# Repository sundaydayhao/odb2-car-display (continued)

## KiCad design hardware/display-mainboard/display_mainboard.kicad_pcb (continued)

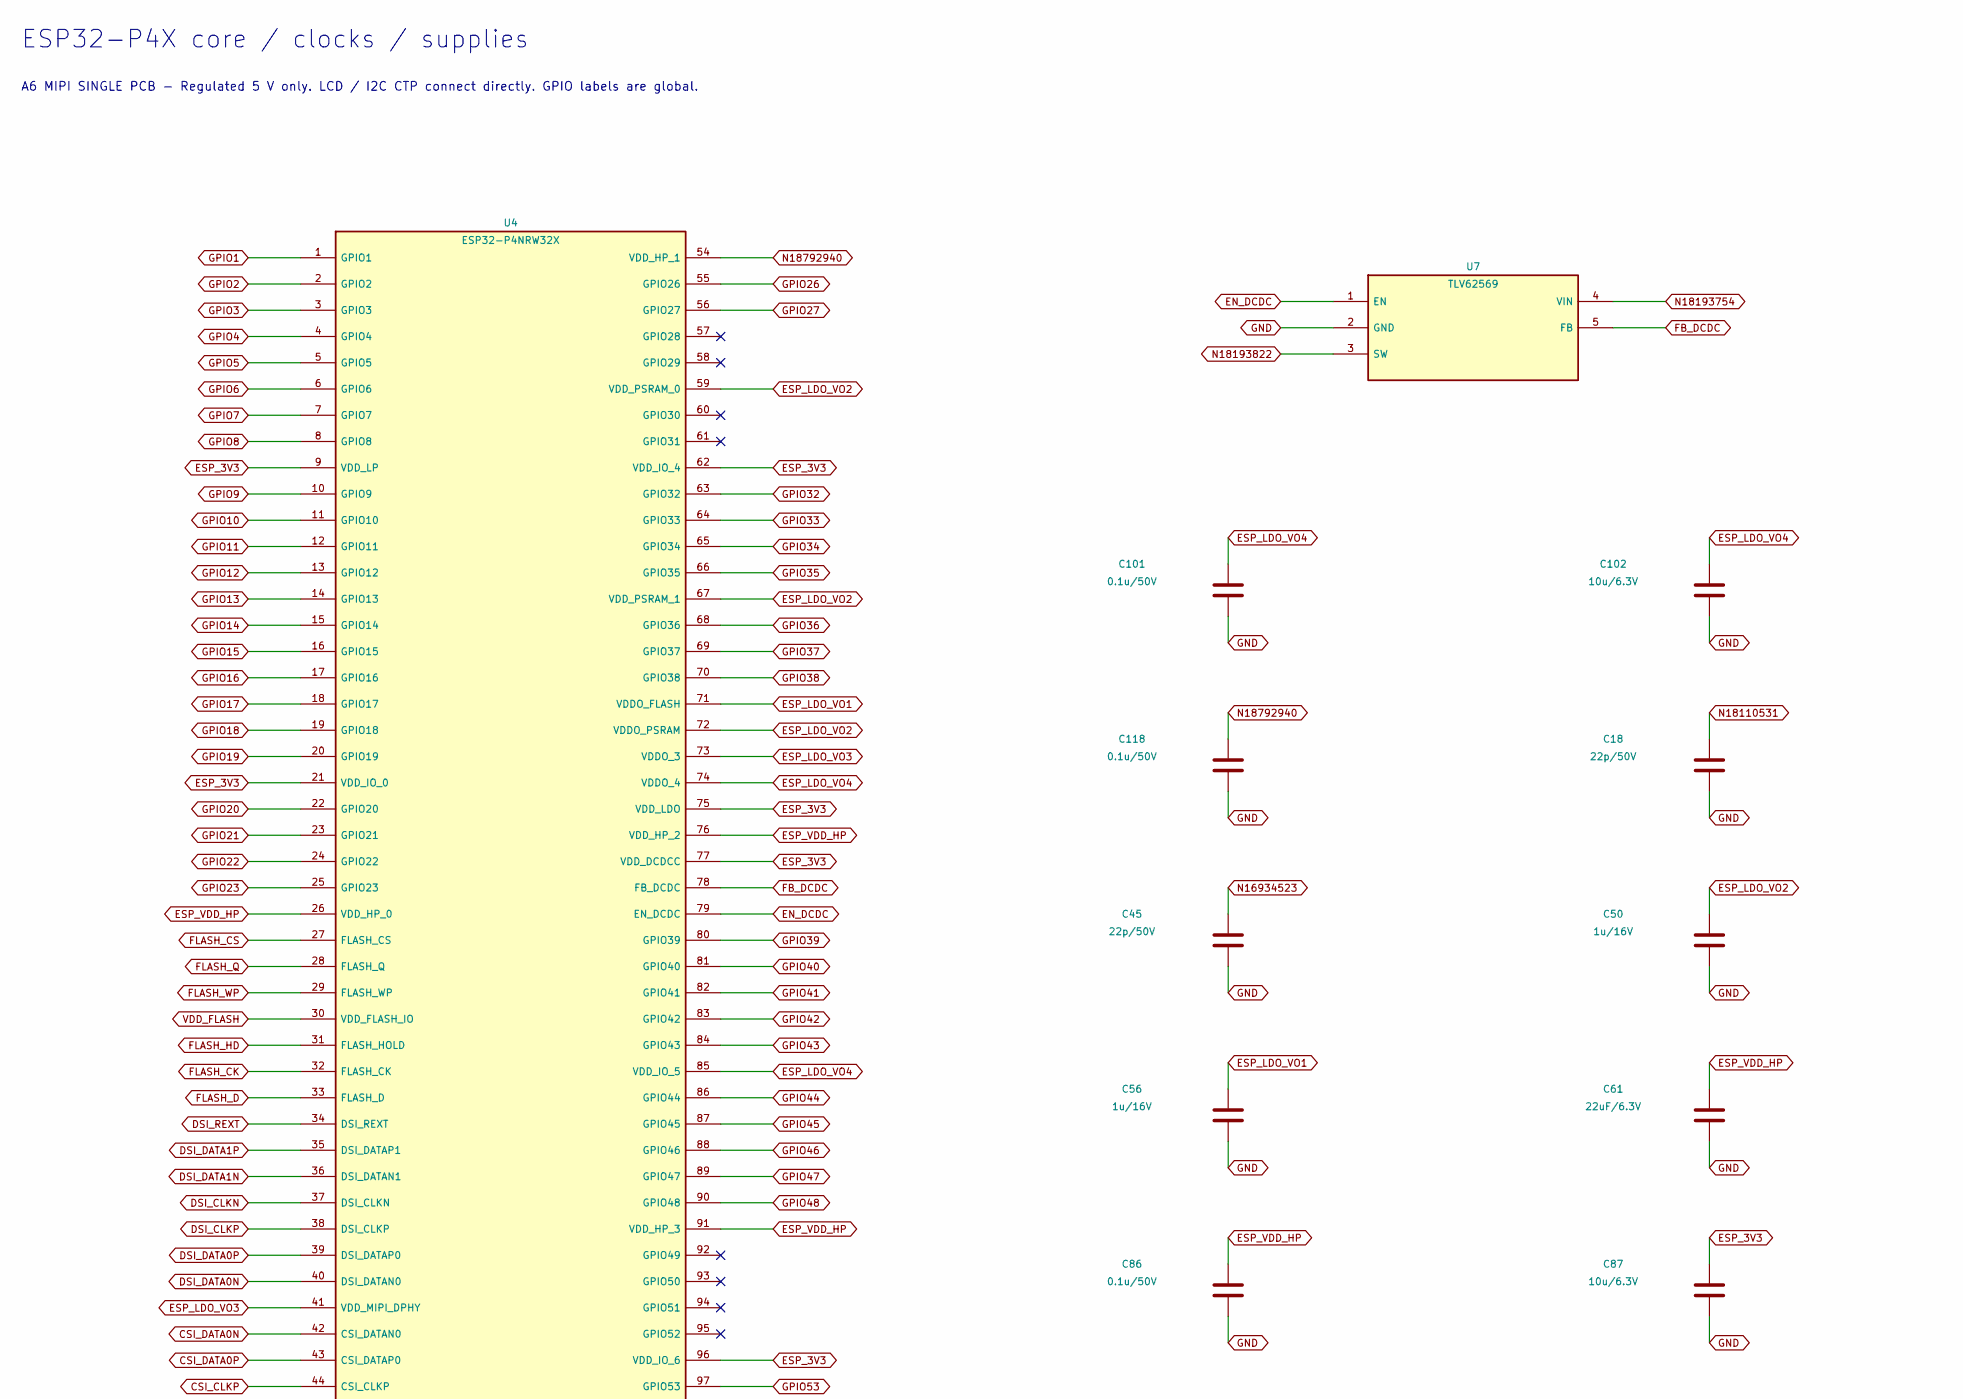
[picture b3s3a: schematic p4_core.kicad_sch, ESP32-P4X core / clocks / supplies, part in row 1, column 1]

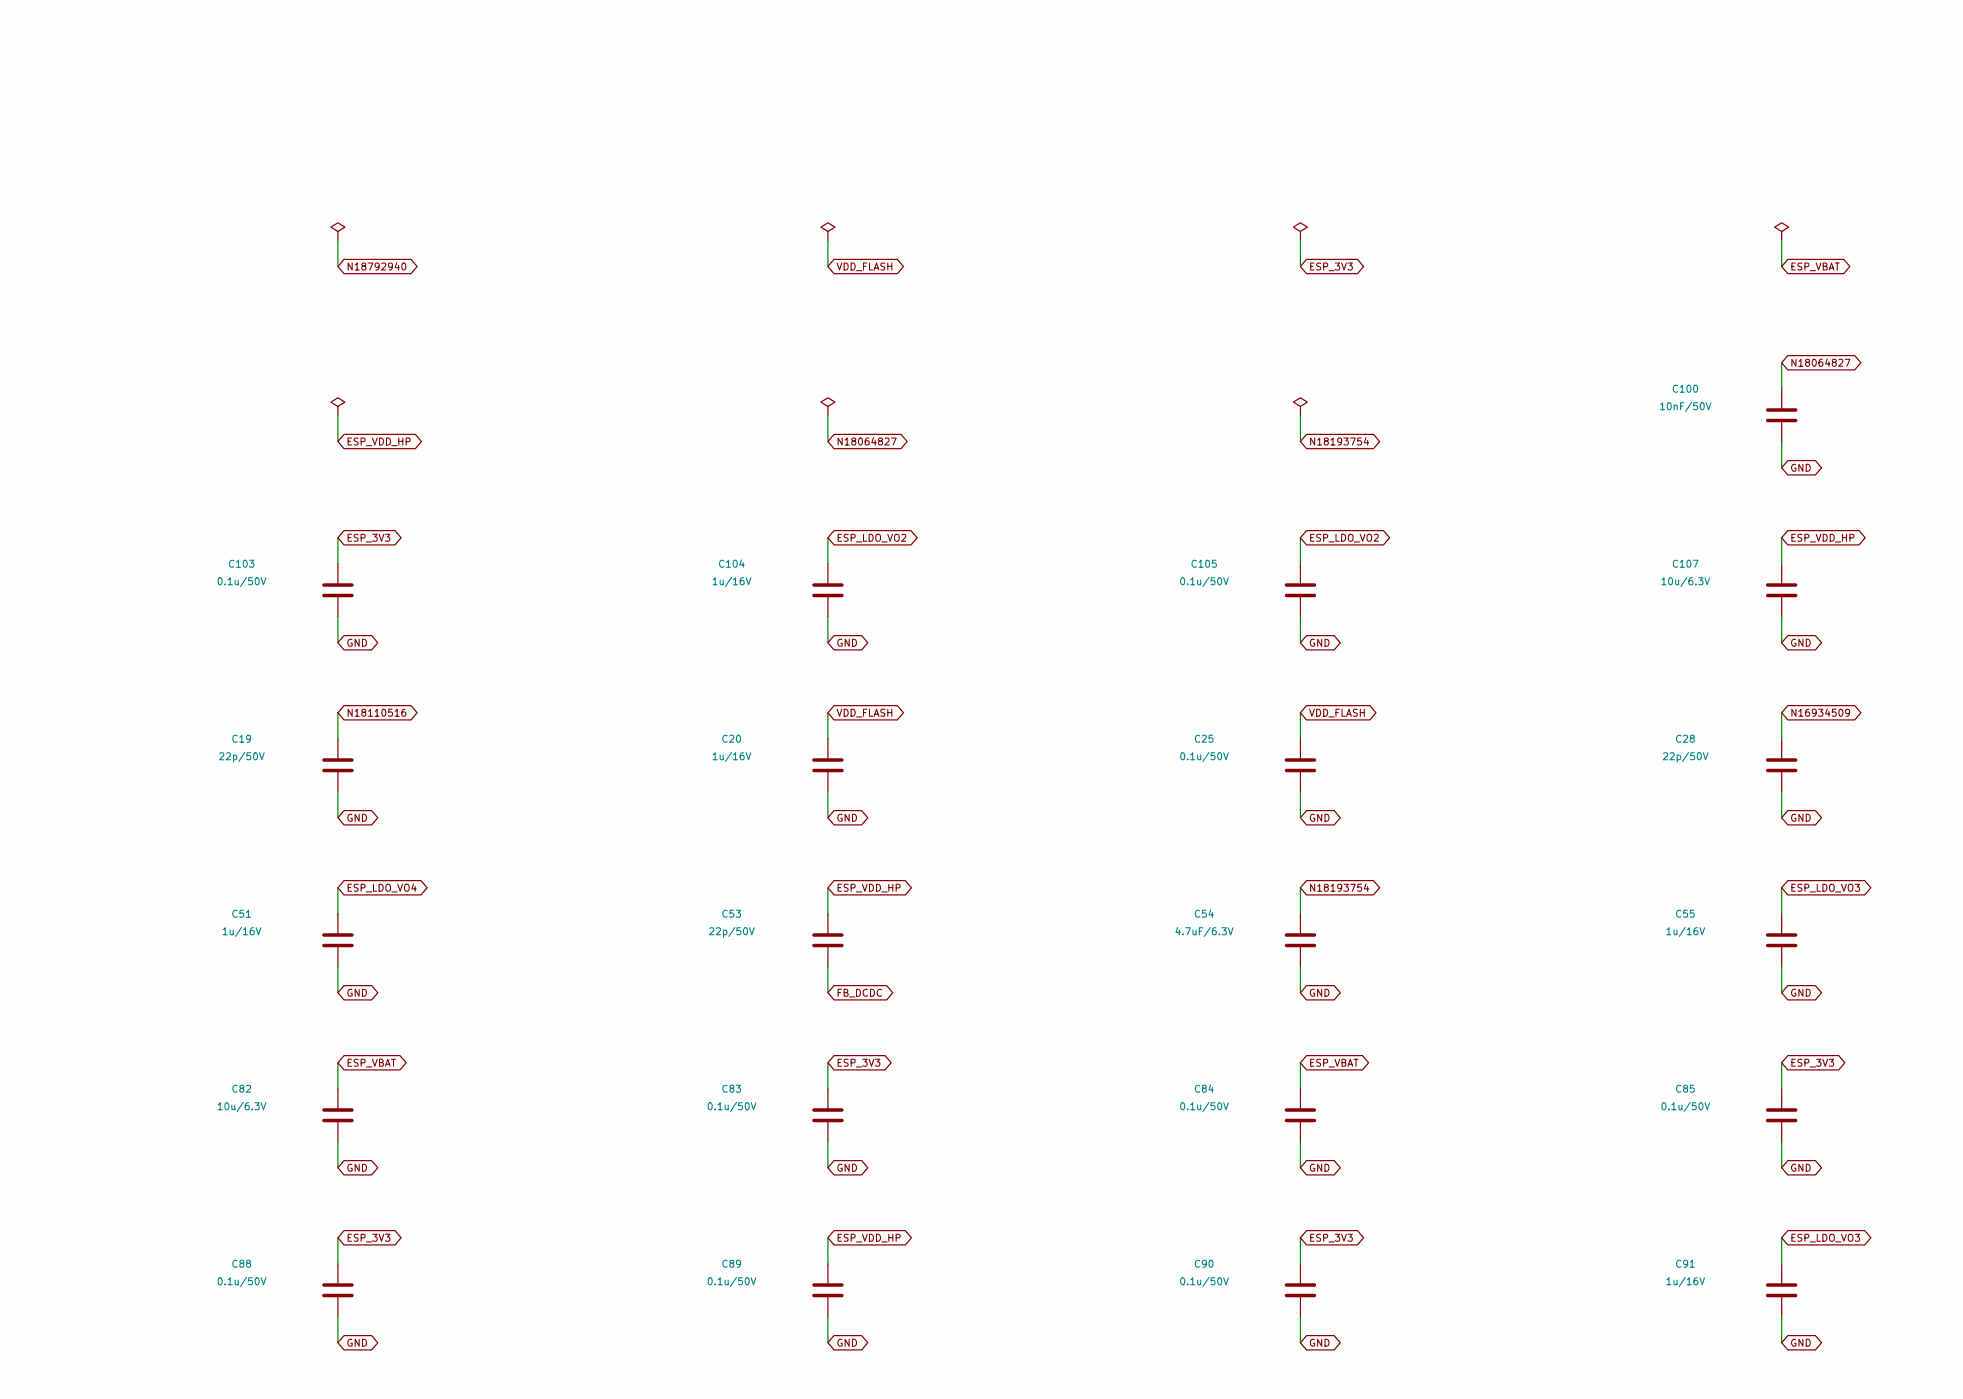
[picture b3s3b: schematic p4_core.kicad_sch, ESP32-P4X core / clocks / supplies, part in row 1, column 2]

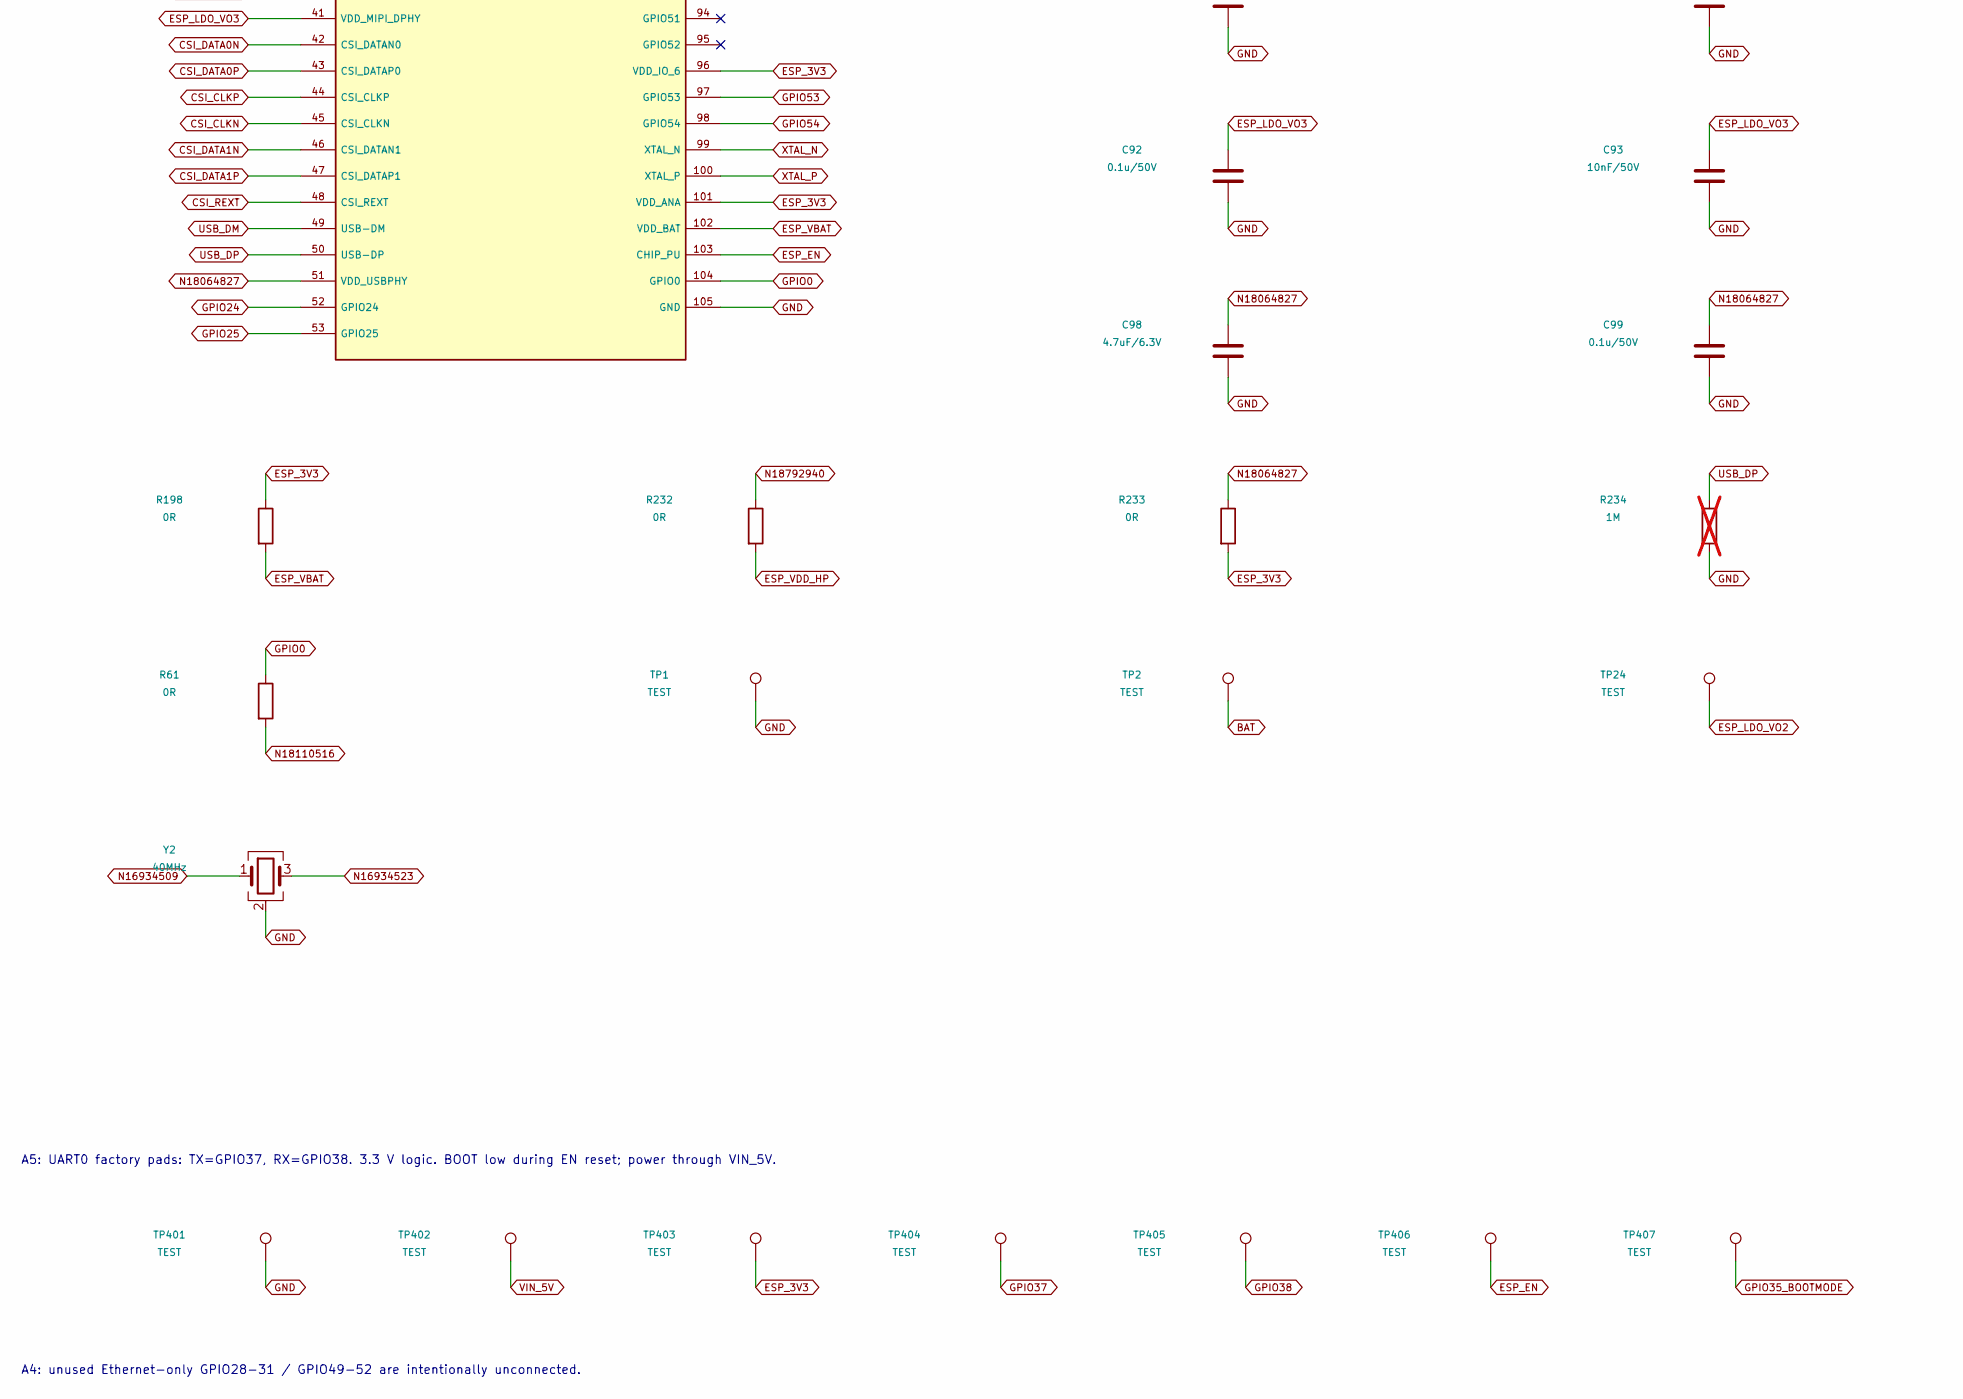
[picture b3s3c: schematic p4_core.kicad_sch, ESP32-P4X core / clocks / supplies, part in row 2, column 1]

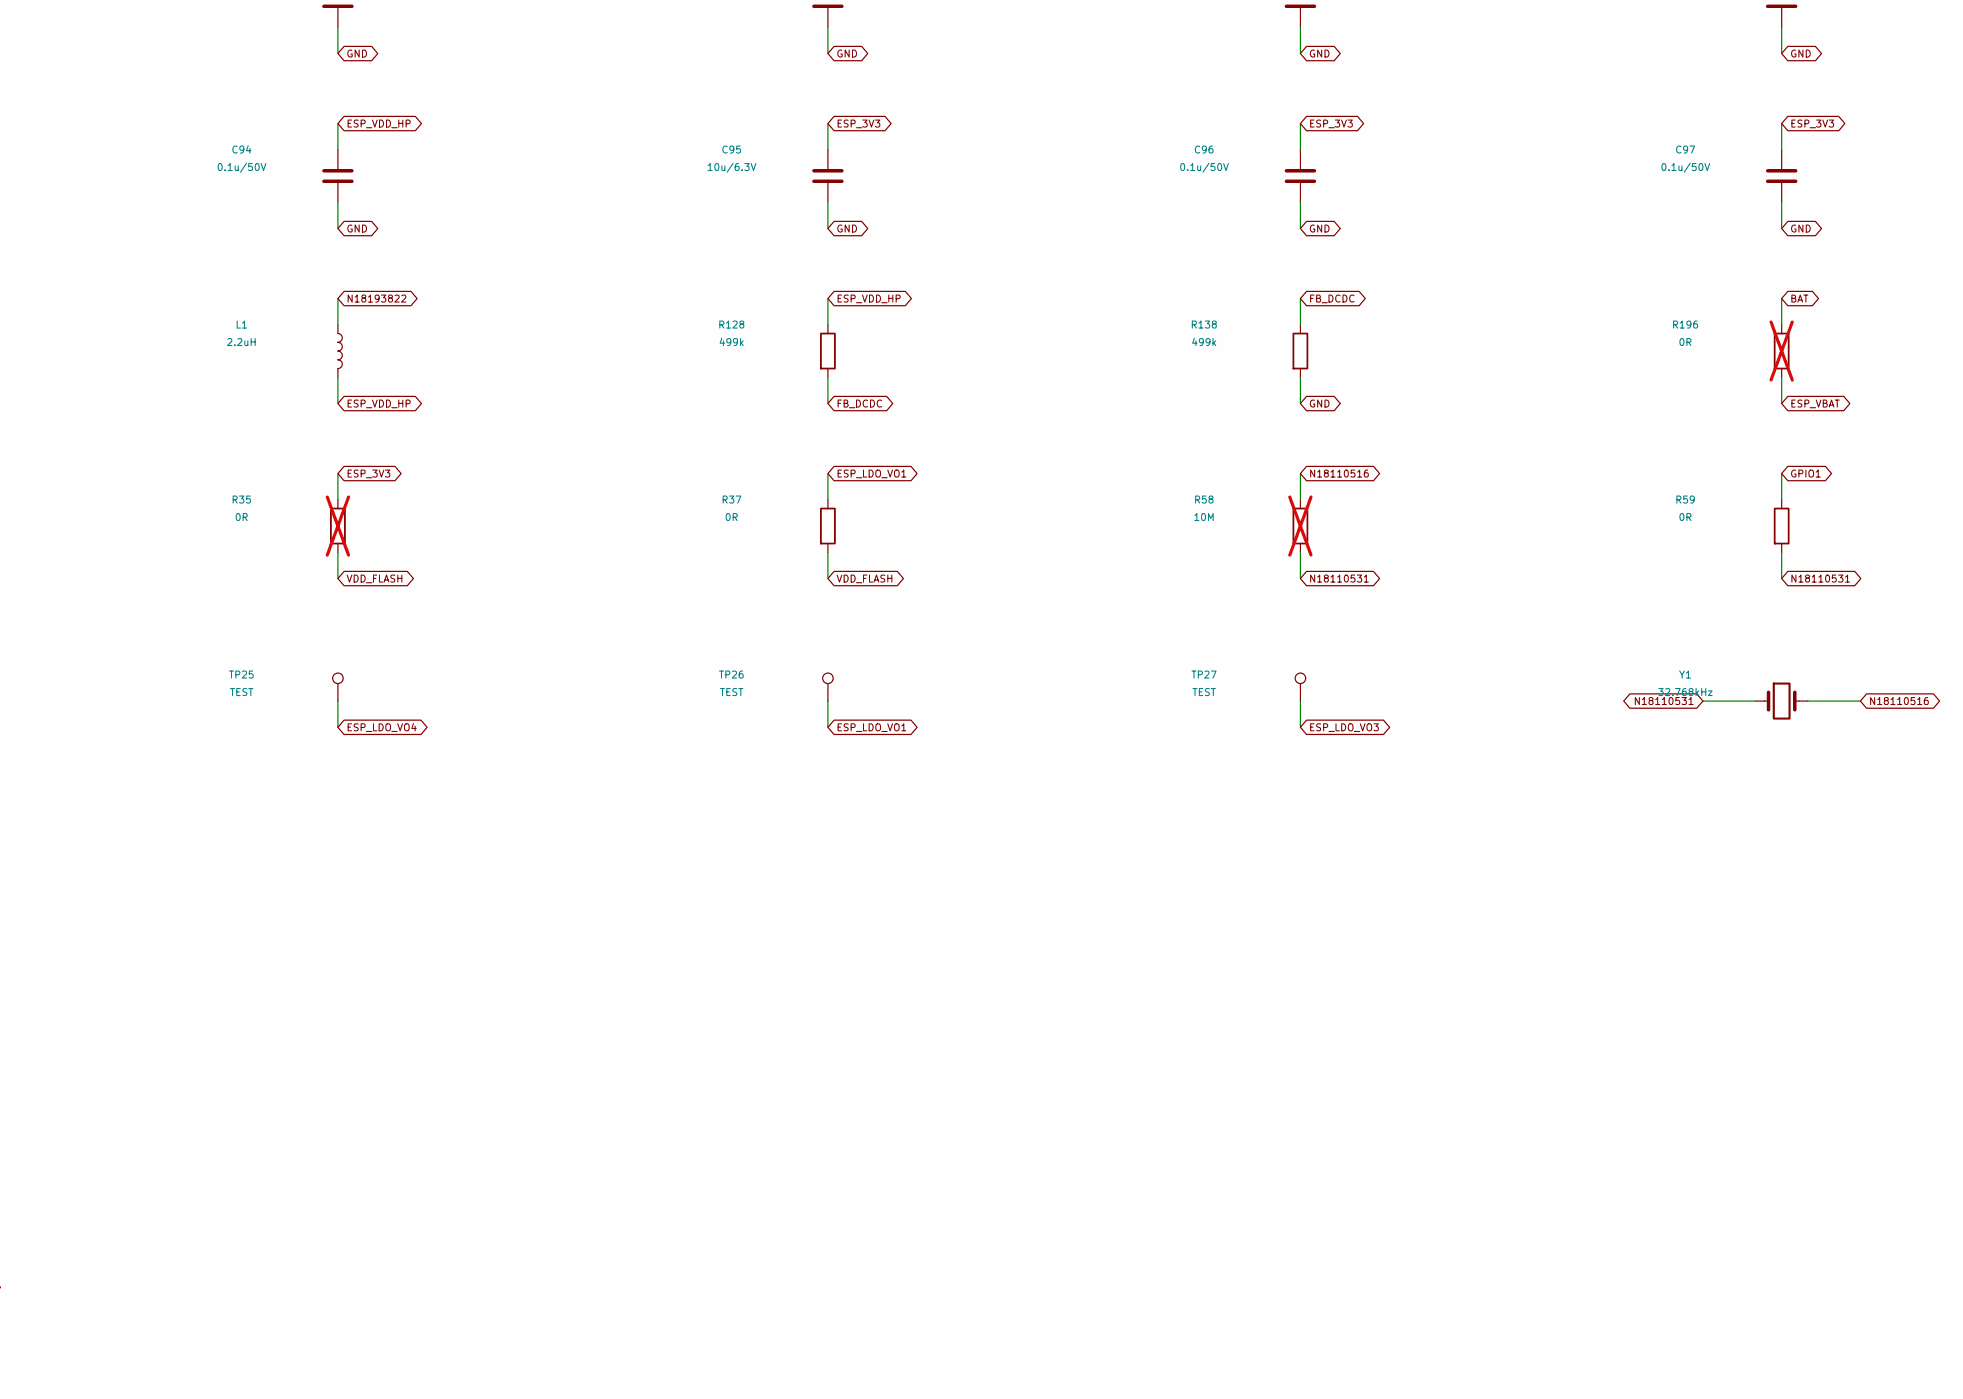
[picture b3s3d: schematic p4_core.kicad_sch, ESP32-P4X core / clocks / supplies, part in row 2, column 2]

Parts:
C18, C19, C28, C45, C53: 22p/50V; C0402__df1ad35910
C20: 1u/16V; C0402__df1ad35910
C25: 0.1u/50V; C0402__df1ad35910
C50, C51, C55, C56, C91, C104: 1u/16V; C0402_097d4b0b__328ab4e626
C54: 4.7uF/6.3V; C0402__df1ad35910
C61: 22uF/6.3V; C0402__df1ad35910
C82, C87, C95, C102, C107: 10u/6.3V; C0402_097d4b0b__328ab4e626
C83, C84, C85, C86, C88, C89, C90, C92, C94, C96, C97, C99, C101, C103, C105, C118: 0.1u/50V; C0402_097d4b0b__328ab4e626
C93, C100: 10nF/50V; C0402_097d4b0b__328ab4e626
C98: 4.7uF/6.3V; C0402_097d4b0b__328ab4e626
L1: 2.2uH; L2520__31a445bbcb; MPN WPN252010U2R2MT
R35: 0R; R0402__6ca295102a; not fitted
R37, R59, R61: 0R; R0402__6ca295102a
R58: 10M; R0402__6ca295102a; not fitted
R128, R138: 499k; R0402__6ca295102a
R196: 0R; R0402_097d4b0b__c1bfdfccc2; not fitted
R198, R232, R233: 0R; R0402_097d4b0b__c1bfdfccc2
R234: 1M; R0402__6ca295102a; not fitted
TP1, TP2, TP24, TP25, TP26, TP27: TEST; TPC1_fd69f0aa__930cba657a
TP401, TP402, TP403, TP404, TP405, TP406, TP407: TEST; TPC1__56d55e75a0
U4: ESP32-P4NRW32X; QFN104_0P35_10_E7P5_A__4ff47e723c; MPN ESP32-P4NRW32X
U7: TLV62569; SOT23_0P95_2P6__29960399d6; MPN TLV62569DBVR
Y1: 32.768kHz; XTAL3215__6c6f8c0a53; MPN SF32K32768D31T-12.5
Y2: 40MHz; XTAL3225__30de0c1c1f; MPN 2.3.3.400001552EL

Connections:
BAT: R196.1, TP2.1
CSI_CLKN: U4.45 (CSI_CLKN); also elsewhere on the board
CSI_CLKP: U4.44 (CSI_CLKP); also elsewhere on the board
CSI_DATA0N: U4.42 (CSI_DATAN0); also elsewhere on the board
CSI_DATA0P: U4.43 (CSI_DATAP0); also elsewhere on the board
CSI_DATA1N: U4.46 (CSI_DATAN1); also elsewhere on the board
CSI_DATA1P: U4.47 (CSI_DATAP1); also elsewhere on the board
CSI_REXT: U4.48 (CSI_REXT); also elsewhere on the board
DSI_CLKN: U4.37 (DSI_CLKN); also elsewhere on the board
DSI_CLKP: U4.38 (DSI_CLKP); also elsewhere on the board
DSI_DATA0N: U4.40 (DSI_DATAN0); also elsewhere on the board
DSI_DATA0P: U4.39 (DSI_DATAP0); also elsewhere on the board
DSI_DATA1N: U4.36 (DSI_DATAN1); also elsewhere on the board
DSI_DATA1P: U4.35 (DSI_DATAP1); also elsewhere on the board
DSI_REXT: U4.34 (DSI_REXT); also elsewhere on the board
EN_DCDC: U4.79 (EN_DCDC), U7.1 (EN)
ESP_3V3: C83.1, C85.1, C87.1, C88.1, C90.1, C95.1, C96.1, C97.1, C103.1, R35.1, R198.1, R233.2, TP403.1, U4.9 (VDD_LP), U4.21 (VDD_IO_0), U4.62 (VDD_IO_4), U4.75 (VDD_LDO), U4.77 (VDD_DCDCC), U4.96 (VDD_IO_6), U4.101 (VDD_ANA); also elsewhere on the board
ESP_EN: TP406.1, U4.103 (CHIP_PU); also elsewhere on the board
ESP_LDO_VO1: C56.1, R37.1, TP26.1, U4.71 (VDDO_FLASH)
ESP_LDO_VO2: C50.1, C104.1, C105.1, TP24.1, U4.59 (VDD_PSRAM_0), U4.67 (VDD_PSRAM_1), U4.72 (VDDO_PSRAM)
ESP_LDO_VO3: C55.1, C91.1, C92.1, C93.1, TP27.1, U4.41 (VDD_MIPI_DPHY), U4.73 (VDDO_3)
ESP_LDO_VO4: C51.1, C101.1, C102.1, TP25.1, U4.74 (VDDO_4), U4.85 (VDD_IO_5); also elsewhere on the board
ESP_VBAT: C82.1, C84.1, R196.2, R198.2, U4.102 (VDD_BAT); also elsewhere on the board
ESP_VDD_HP: C53.1, C61.1, C86.1, C89.1, C94.1, C107.1, L1.2, R128.1, R232.2, U4.26 (VDD_HP_0), U4.76 (VDD_HP_2), U4.91 (VDD_HP_3)
FB_DCDC: C53.2, R128.2, R138.1, U4.78 (FB_DCDC), U7.5 (FB)
FLASH_CK: U4.32 (FLASH_CK); also elsewhere on the board
FLASH_CS: U4.27 (FLASH_CS); also elsewhere on the board
FLASH_D: U4.33 (FLASH_D); also elsewhere on the board
FLASH_HD: U4.31 (FLASH_HOLD); also elsewhere on the board
FLASH_Q: U4.28 (FLASH_Q); also elsewhere on the board
FLASH_WP: U4.29 (FLASH_WP); also elsewhere on the board
GPIO0: R61.1, U4.104 (GPIO0); also elsewhere on the board
GPIO1: R59.1, U4.1 (GPIO1); also elsewhere on the board
GPIO2: U4.2 (GPIO2); also elsewhere on the board
GPIO3: U4.3 (GPIO3); also elsewhere on the board
GPIO4: U4.4 (GPIO4); also elsewhere on the board
GPIO5: U4.5 (GPIO5); also elsewhere on the board
GPIO6: U4.6 (GPIO6); also elsewhere on the board
GPIO7: U4.7 (GPIO7); also elsewhere on the board
GPIO8: U4.8 (GPIO8); also elsewhere on the board
GPIO9: U4.10 (GPIO9); also elsewhere on the board
GPIO10: U4.11 (GPIO10); also elsewhere on the board
GPIO11: U4.12 (GPIO11); also elsewhere on the board
GPIO12: U4.13 (GPIO12); also elsewhere on the board
GPIO13: U4.14 (GPIO13); also elsewhere on the board
GPIO14: U4.15 (GPIO14); also elsewhere on the board
GPIO15: U4.16 (GPIO15); also elsewhere on the board
GPIO16: U4.17 (GPIO16); also elsewhere on the board
GPIO17: U4.18 (GPIO17); also elsewhere on the board
GPIO18: U4.19 (GPIO18); also elsewhere on the board
GPIO19: U4.20 (GPIO19); also elsewhere on the board
GPIO20: U4.22 (GPIO20); also elsewhere on the board
GPIO21: U4.23 (GPIO21); also elsewhere on the board
GPIO22: U4.24 (GPIO22); also elsewhere on the board
GPIO23: U4.25 (GPIO23); also elsewhere on the board
GPIO24: U4.52 (GPIO24); also elsewhere on the board
GPIO25: U4.53 (GPIO25); also elsewhere on the board
GPIO26: U4.55 (GPIO26); also elsewhere on the board
GPIO27: U4.56 (GPIO27); also elsewhere on the board
GPIO28: U4.57 (GPIO28); also elsewhere on the board
GPIO29: U4.58 (GPIO29); also elsewhere on the board
GPIO30: U4.60 (GPIO30); also elsewhere on the board
GPIO31: U4.61 (GPIO31); also elsewhere on the board
GPIO32: U4.63 (GPIO32); also elsewhere on the board
GPIO33: U4.64 (GPIO33); also elsewhere on the board
GPIO34: U4.65 (GPIO34); also elsewhere on the board
GPIO35: U4.66 (GPIO35); also elsewhere on the board
GPIO36: U4.68 (GPIO36); also elsewhere on the board
GPIO37: TP404.1, U4.69 (GPIO37); also elsewhere on the board
GPIO38: TP405.1, U4.70 (GPIO38); also elsewhere on the board
GPIO39: U4.80 (GPIO39); also elsewhere on the board
GPIO40: U4.81 (GPIO40); also elsewhere on the board
GPIO41: U4.82 (GPIO41); also elsewhere on the board
GPIO42: U4.83 (GPIO42); also elsewhere on the board
GPIO43: U4.84 (GPIO43); also elsewhere on the board
GPIO44: U4.86 (GPIO44); also elsewhere on the board
GPIO45: U4.87 (GPIO45); also elsewhere on the board
GPIO46: U4.88 (GPIO46); also elsewhere on the board
GPIO47: U4.89 (GPIO47); also elsewhere on the board
GPIO48: U4.90 (GPIO48); also elsewhere on the board
GPIO49: U4.92 (GPIO49); also elsewhere on the board
GPIO50: U4.93 (GPIO50); also elsewhere on the board
GPIO51: U4.94 (GPIO51); also elsewhere on the board
GPIO52: U4.95 (GPIO52); also elsewhere on the board
GPIO53: U4.97 (GPIO53); also elsewhere on the board
GPIO54: U4.98 (GPIO54); also elsewhere on the board
N16934509: C28.1, Y2.1; also elsewhere on the board
N16934523: C45.1, Y2.3; also elsewhere on the board
N18064827: C98.1, C99.1, C100.1, R233.1, U4.51 (VDD_USBPHY)
N18110516: C19.1, R58.1, R61.2, Y1.2
N18110531: C18.1, R58.2, R59.2, Y1.1
N18193754: C54.1, U7.4 (VIN); also elsewhere on the board
N18193822: L1.1, U7.3 (SW)
N18792940: C118.1, R232.1, U4.54 (VDD_HP_1)
USB_DM: U4.49 (USB-DM); also elsewhere on the board
USB_DP: R234.1, U4.50 (USB-DP); also elsewhere on the board
VDD_FLASH: C20.1, C25.1, R35.2, R37.2, U4.30 (VDD_FLASH_IO); also elsewhere on the board
XTAL_N: U4.99 (XTAL_N); also elsewhere on the board
XTAL_P: U4.100 (XTAL_P); also elsewhere on the board

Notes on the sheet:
ESP32-P4X core / clocks / supplies
A6 MIPI SINGLE PCB - Regulated 5 V only. LCD / I2C CTP connect directly. GPIO labels are global.
A4: unused Ethernet-only GPIO28-31 / GPIO49-52 are intentionally unconnected.
A5: UART0 factory pads: TX=GPIO37, RX=GPIO38. 3.3 V logic. BOOT low during EN reset; power through VIN_5V.
